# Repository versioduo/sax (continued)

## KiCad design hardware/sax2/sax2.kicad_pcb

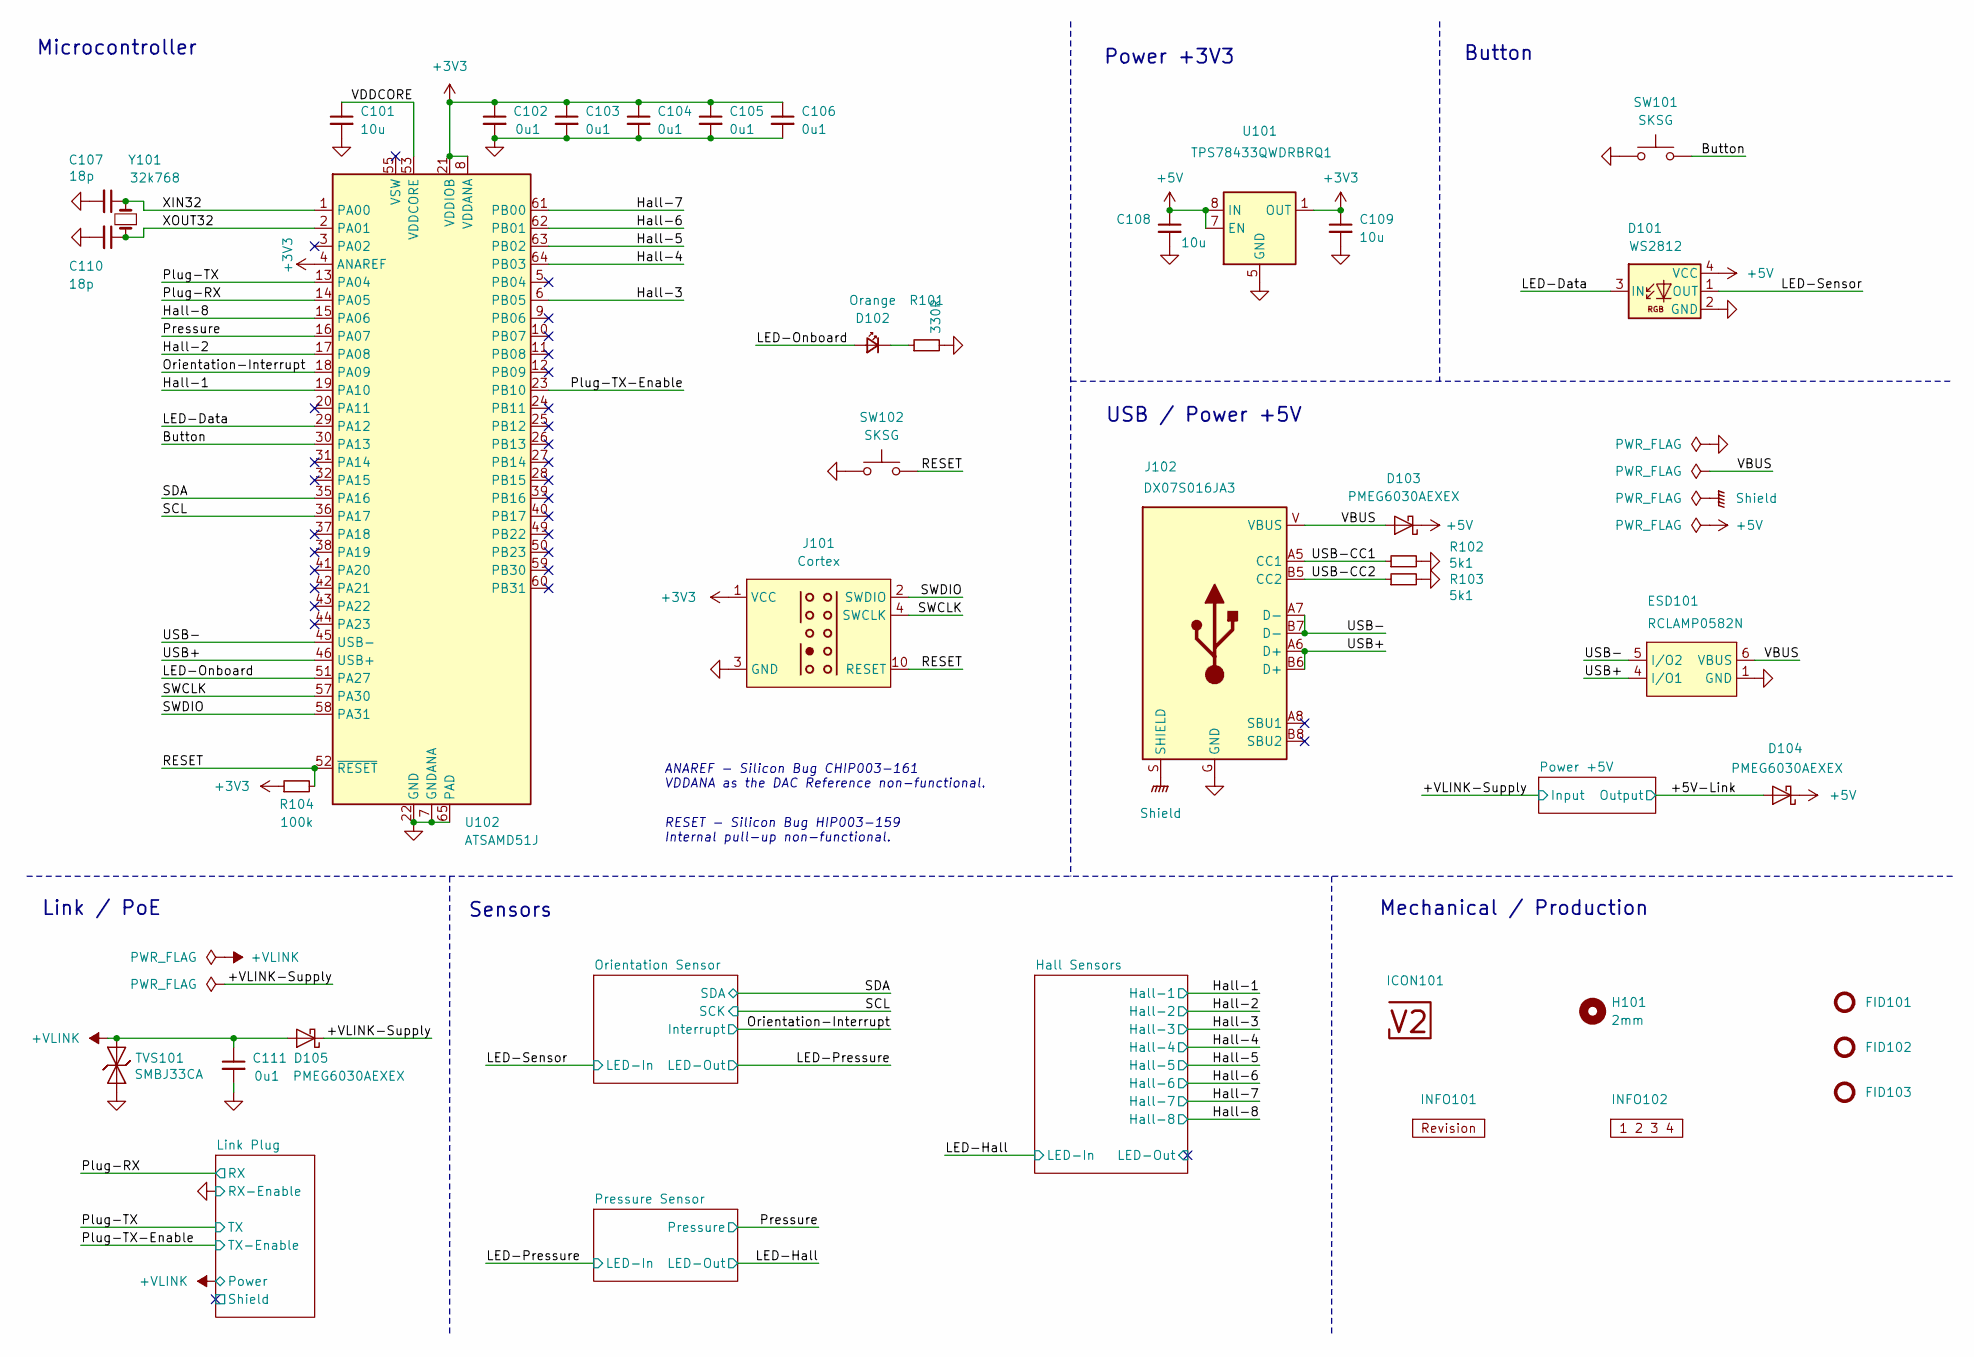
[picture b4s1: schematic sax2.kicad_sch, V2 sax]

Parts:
C101: 10u; C_0603; Rating 10V; Mouser 810-C1608X6S1A106M
C102, C103, C104, C105, C106, C111: 0u1; C_0603; Rating 50V; Mouser 810-CGA3E2X7R1H104MA
C107, C110: 18p; C_0603; Mouser 603-CC603JRNPO9BN180
C108, C109: 10u; C_0805; Rating 25V; Mouser 810-C2012X5R1E106K
D101: WS2812; WS2812-2020; LCSC C965555
D102: Orange; LED_0603; Mouser 755-SML-D12D1WT86
D103, D104, D105: PMEG6030AEXEX; D_SOD-123HP; Mouser 771-PMEG6030AEXEX
ESD101: RCLAMP0582N; SLP1210N6; Mouser 947-RCLAMP0582N.TCT
FID101, FID102, FID103: Fiducial_Paste; Fiducial_0.5mm_Mask1mm_Paste
H101: 2mm; MountingHole_2mm
ICON101: V2-logo; Logo_Small
INFO101: Revision
INFO102: Layer_Numbers
J101: Cortex
J102: DX07S016JA3; JAE_DX07S016JA3; Mouser 656-DX07S016JA3R1500
R101: 330R; R_0603; Rating 100mW; Mouser 71-CRCW0603330RFKEAC
R102, R103: 5k1; R_0603; Rating 100mW; Mouser 71-CRCW06035K10FKEAC
R104: 100k; R_0603; Rating 100mW; Mouser 71-CRCW0603100KFKEAC
SW101, SW102: SKSG; Mouser 688-SKSGACE010
TVS101: SMBJ33CA; D_SMB; Rating 33V; Mouser 652-SMBJ33CA-Q
U101: TPS78433QWDRBRQ1; VSON-8-1_3x3mm_P0.65_EP1.65x2.4mm; Mouser 595-TPS78433QWDRBRQ1
U102: ATSAMD51J; QFN-64-1EP_9x9mm_P0.5mm_EP4.8x4.8mm_ThermalVias; Mouser 556-ATSAMD51J19AMU
Y101: 32k768; Crystal_SMD_3215-2Pin_3.2x1.5mm; Mouser 815-ABS0716632.768KT

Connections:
+3V3: C102.1, C103.1, C104.1, C105.1, C106.1, C109.1, J101.1 (VCC), R104.1, U101.1 (OUT), U102.4 (ANAREF), U102.8 (VDDANA), U102.21 (VDDIOB), U102.34 (VDDIO), U102.48 (VDDIO), U102.56 (VDDIO); also elsewhere on the board
+5V: C108.1, D101.4 (VCC), D103.1 (K), D104.1 (K), U101.7 (EN), U101.8 (IN); also elsewhere on the board
+VLINK: C111.1, D105.2 (A), TVS101.2 (A); also elsewhere on the board
/+5V-Link: D104.2 (A); also elsewhere on the board
/+VLINK-Supply: D105.1 (K); also elsewhere on the board
/Button: SW101.2, U102.30 (PA13)
/Hall-1: U102.19 (PA10); also elsewhere on the board
/Hall-2: U102.17 (PA08); also elsewhere on the board
/Hall-3: U102.6 (PB05); also elsewhere on the board
/Hall-4: U102.64 (PB03); also elsewhere on the board
/Hall-5: U102.63 (PB02); also elsewhere on the board
/Hall-6: U102.62 (PB01); also elsewhere on the board
/Hall-7: U102.61 (PB00); also elsewhere on the board
/Hall-8: U102.15 (PA06); also elsewhere on the board
/LED-Data: D101.3 (IN), U102.29 (PA12)
/LED-Onboard: D102.2 (A), U102.51 (PA27)
/LED-Sensor: D101.1 (OUT); also elsewhere on the board
/Orientation-Interrupt: U102.18 (PA09); also elsewhere on the board
/Plug-RX: U102.14 (PA05); also elsewhere on the board
/Plug-TX: U102.13 (PA04); also elsewhere on the board
/Plug-TX-Enable: U102.23 (PB10); also elsewhere on the board
/Pressure: U102.16 (PA07); also elsewhere on the board
/RESET: J101.10 (RESET), R104.2, SW102.2, U102.52 (~RESET)
/SCL: U102.36 (PA17); also elsewhere on the board
/SDA: U102.35 (PA16); also elsewhere on the board
/SWCLK: J101.4 (SWCLK), U102.57 (PA30)
/SWDIO: J101.2 (SWDIO), U102.58 (PA31)
/USB+: ESD101.4 (I/O1), J102.A6 (D+), J102.B6 (D+), U102.46 (USB+)
/USB-: ESD101.5 (I/O2), J102.A7 (D-), J102.B7 (D-), U102.45 (USB-)
/USB-CC1: J102.A5 (CC1), R102.1
/USB-CC2: J102.B5 (CC2), R103.1
/VBUS: D103.2 (A), ESD101.6 (VBUS), J102.V (VBUS)
/VDDCORE: C101.1, U102.53 (VDDCORE)
/XIN32: C107.1, U102.1 (PA00), Y101.2
/XOUT32: C110.1, U102.2 (PA01), Y101.1
GND: C101.2, C102.2, C103.2, C104.2, C105.2, C106.2, C107.2, C108.2, C109.2, C110.2, C111.2, D101.2 (GND), ESD101.1 (GND), J101.3 (GND), J101.5 (GND), J102.G (GND), R101.2, R102.2, R103.2, SW101.1, SW102.1, TVS101.1 (K), U101.5 (GND), U101.9 (GND), U102.7 (GNDANA), U102.22 (GND), U102.33 (GND), U102.47 (GND), U102.54 (GND), U102.65 (PAD); also elsewhere on the board
unnamed: D102.1 (K), R101.1
Shield: J102.S (SHIELD)

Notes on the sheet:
ANAREF - Silicon Bug CHIP003-161 VDDANA as the DAC Reference non-functional.
Sensors
Link / PoE
RESET - Silicon Bug HIP003-159 Internal pull-up non-functional.
Button
Power +3V3
Mechanical / Production
Microcontroller
USB / Power +5V

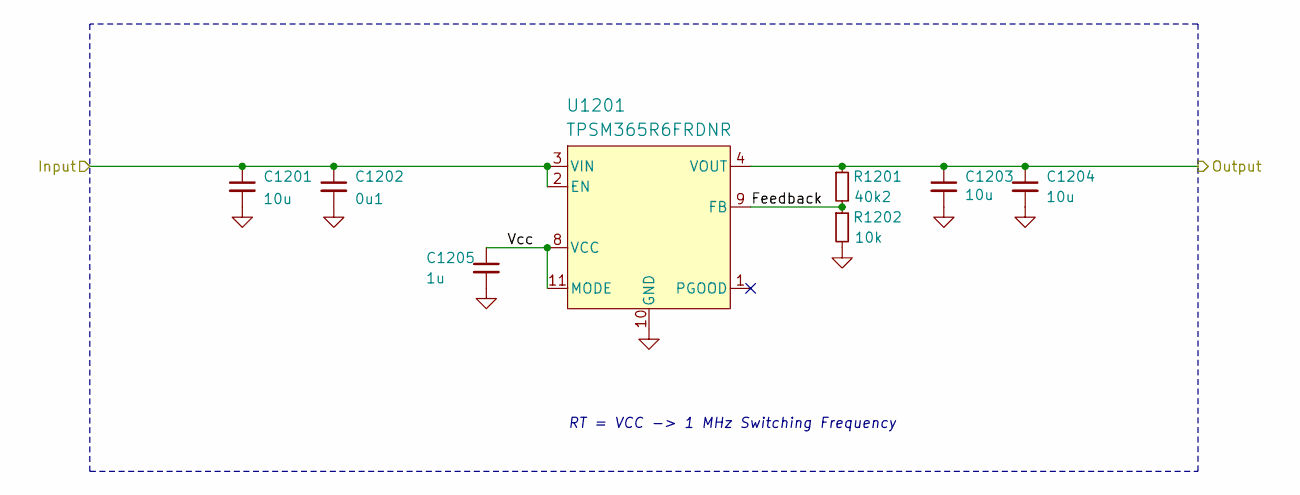
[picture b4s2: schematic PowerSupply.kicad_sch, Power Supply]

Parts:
C1201: 10u; C_1210; Rating 50V; Mouser 810-CNA6P1X7R1H106K2
C1202: 0u1; C_0603; Rating 50V; Mouser 810-CGA3E2X7R1H104MA
C1203, C1204: 10u; C_1210; Rating 25V; Mouser 810-CGA6P3X7R1E226M5
C1205: 1u; C_0603; Rating 50V; Mouser 810-CGA3E3X7R1H105K0
R1201: 40k2; R_0603; Rating 500mW; Mouser 71-RCS060340K2FKEA
R1202: 10k; R_0603; Rating 100mW; Mouser 71-CRCW060310K0FKEAC
U1201: TPSM365R6FRDNR; QFN-11; Rating 600mA; Mouser 595-TPSM365R6FRDNR

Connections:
/+5V-Link: C1203.1, C1204.1, R1201.1, U1201.4 (VOUT); also elsewhere on the board
/+VLINK-Supply: C1201.1, C1202.1, U1201.2 (EN), U1201.3 (VIN); also elsewhere on the board
/Power +5V/Feedback: R1201.2, R1202.1, U1201.9 (FB)
/Power +5V/Vcc: C1205.1, U1201.8 (VCC), U1201.11 (MODE)
GND: C1201.2, C1202.2, C1203.2, C1204.2, C1205.2, R1202.2, U1201.10 (GND); also elsewhere on the board

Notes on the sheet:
RT = VCC -> 1 MHz Switching Frequency

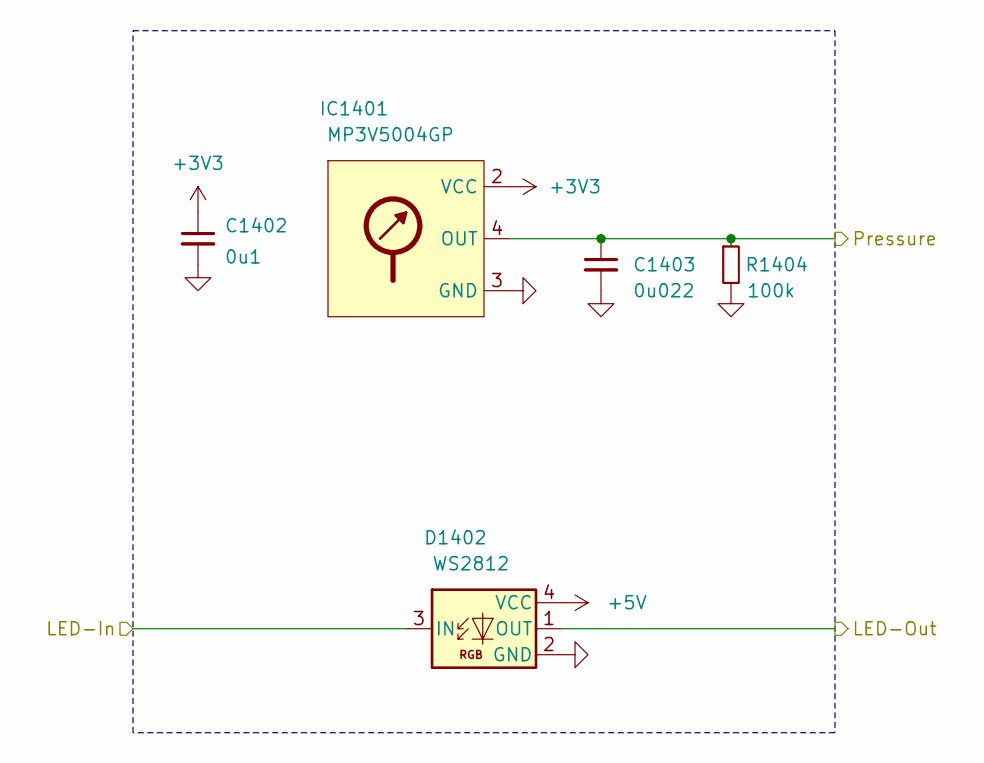
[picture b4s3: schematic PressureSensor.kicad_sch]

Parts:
C1402: 0u1; C_0603; Rating 50V; Mouser 810-CGA3E2X7R1H104MA
C1403: 0u022; C_0603; Mouser 603-CC603KPX7R9BB223
D1402: WS2812; WS2812-2020; LCSC C965555
IC1401: MP3V5004GP; Mouser 841-MP3V5004GP
R1404: 100k; R_0603; Rating 100mW; Mouser 71-CRCW0603100KFKEAC

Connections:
+3V3: C1402.1, IC1401.2 (VCC); also elsewhere on the board
+5V: D1402.4 (VCC); also elsewhere on the board
/LED-Hall: D1402.1 (OUT); also elsewhere on the board
/LED-Pressure: D1402.3 (IN); also elsewhere on the board
/Pressure: C1403.1, IC1401.4 (OUT), R1404.1; also elsewhere on the board
GND: C1402.2, C1403.2, D1402.2 (GND), IC1401.3 (GND), R1404.2; also elsewhere on the board

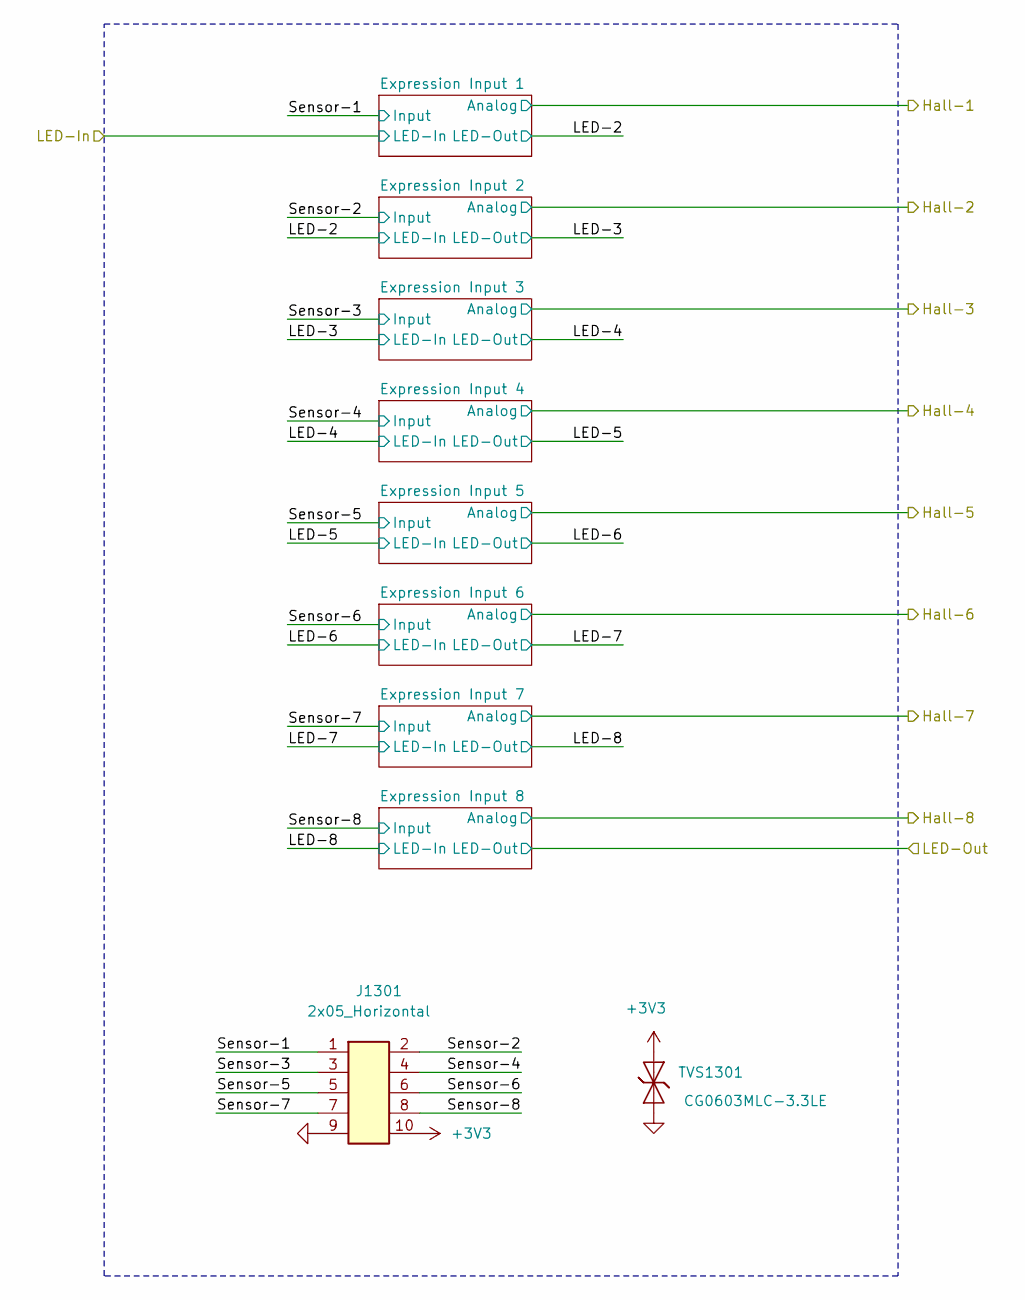
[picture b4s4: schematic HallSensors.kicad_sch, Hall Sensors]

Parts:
J1301: 2x05_Horizontal; PinHeader_2x05_P1.27mm_Horizontal; Mouser 649-200211120001T4LF
TVS1301: CG0603MLC-3.3LE; D_0603; Rating 3V3; Mouser 652-CG0603MLC-3.3LE

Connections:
+3V3: J1301.10, TVS1301.1 (K); also elsewhere on the board
/Hall Sensors/Sensor-1: J1301.1; also elsewhere on the board
/Hall Sensors/Sensor-2: J1301.2; also elsewhere on the board
/Hall Sensors/Sensor-3: J1301.3; also elsewhere on the board
/Hall Sensors/Sensor-4: J1301.4; also elsewhere on the board
/Hall Sensors/Sensor-5: J1301.5; also elsewhere on the board
/Hall Sensors/Sensor-6: J1301.6; also elsewhere on the board
/Hall Sensors/Sensor-7: J1301.7; also elsewhere on the board
/Hall Sensors/Sensor-8: J1301.8; also elsewhere on the board
GND: J1301.9, TVS1301.2 (A); also elsewhere on the board

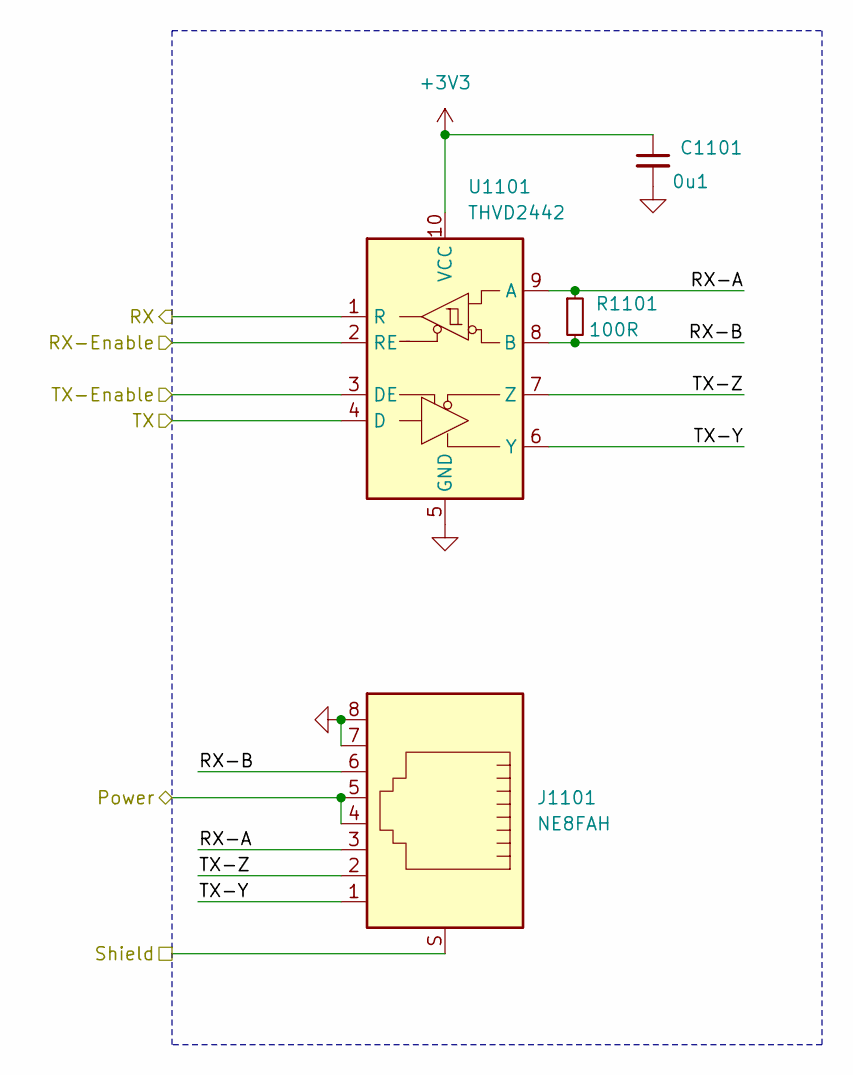
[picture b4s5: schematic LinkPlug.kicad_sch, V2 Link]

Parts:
C1101: 0u1; C_0603; Rating 50V; Mouser 810-CGA3E2X7R1H104MA
J1101: NE8FAH; Mouser 568-NE8FAH
R1101: 100R; R_0603; Rating 330mW; Mouser 71-CRCW0603100RFKEAH
U1101: THVD2442; VSON-10-4-1EP_3x3mm_P0.5mm_EP1.65x2.4mm_ThermalVias; Mouser 595-THVD2442DRCR

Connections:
+3V3: C1101.1, U1101.10 (VCC); also elsewhere on the board
+VLINK: J1101.4, J1101.5; also elsewhere on the board
/Link Plug/RX-A: J1101.3, R1101.1, U1101.9 (A)
/Link Plug/RX-B: J1101.6, R1101.2, U1101.8 (B)
/Link Plug/Shield: J1101.S
/Link Plug/TX-Y: J1101.1, U1101.6 (Y)
/Link Plug/TX-Z: J1101.2, U1101.7 (Z)
/Plug-RX: U1101.1 (R); also elsewhere on the board
/Plug-TX: U1101.4 (D); also elsewhere on the board
/Plug-TX-Enable: U1101.3 (DE); also elsewhere on the board
GND: C1101.2, J1101.7, J1101.8, U1101.2 (RE), U1101.5 (GND), U1101.11 (GND); also elsewhere on the board

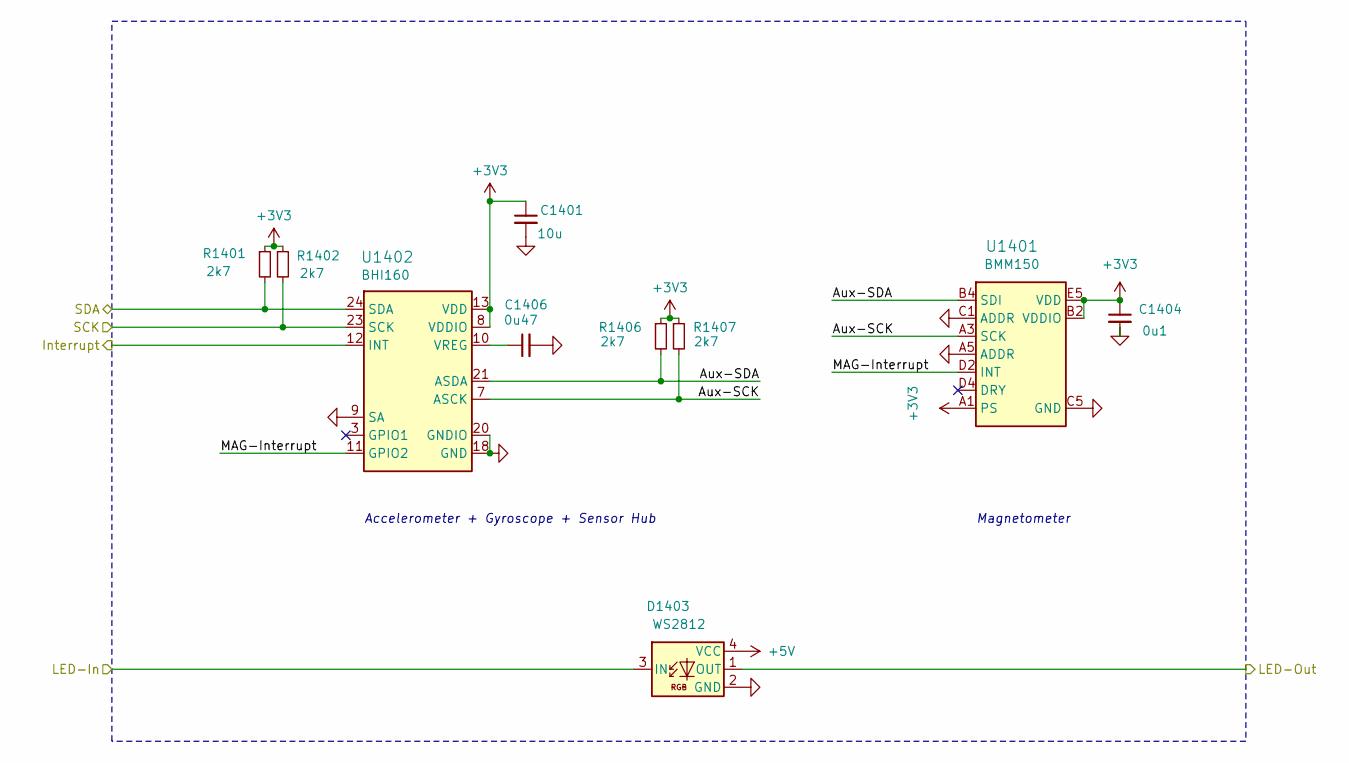
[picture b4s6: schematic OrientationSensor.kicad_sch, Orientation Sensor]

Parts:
C1401: 10u; C_0603; Rating 10V; Mouser 810-C1608X6S1A106M
C1404: 0u1; C_0603; Rating 50V; Mouser 810-CGA3E2X7R1H104MA
C1406: 0u47; C_0603; Mouser 603-CC0603JR6BB474
D1403: WS2812; WS2812-2020; LCSC C965555
R1401, R1402, R1406, R1407: 2k7; R_0603; Rating 100mW; Mouser 71-CRCW06032K70FKEAC
U1401: BMM150; WLCSP-1.56x1.56; LCSC C171681
U1402: BHI160; LGA24-3x3; LCSC C464452

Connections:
+3V3: C1401.1, C1404.1, R1401.1, R1402.1, R1406.1, R1407.1, U1401.A1 (PS), U1401.B2 (VDDIO), U1401.E5 (VDD), U1402.8 (VDDIO), U1402.13 (VDD); also elsewhere on the board
+5V: D1403.4 (VCC); also elsewhere on the board
/LED-Pressure: D1403.1 (OUT); also elsewhere on the board
/LED-Sensor: D1403.3 (IN); also elsewhere on the board
/Orientation Sensor/Aux-SCK: R1407.2, U1401.A3 (SCK), U1402.7 (ASCK)
/Orientation Sensor/Aux-SDA: R1406.2, U1401.B4 (SDI), U1402.21 (ASDA)
/Orientation Sensor/MAG-Interrupt: U1401.D2 (INT), U1402.11 (GPIO2)
/Orientation-Interrupt: U1402.12 (INT); also elsewhere on the board
/SCL: R1402.2, U1402.23 (SCK); also elsewhere on the board
/SDA: R1401.2, U1402.24 (SDA); also elsewhere on the board
GND: C1401.2, C1404.2, C1406.2, D1403.2 (GND), U1401.A5 (ADDR), U1401.C1 (ADDR), U1401.C5 (GND), U1401.E1 (GND), U1401.E3 (GND), U1402.9 (SA), U1402.18 (GND), U1402.20 (GNDIO); also elsewhere on the board
unnamed: C1406.1, U1402.10 (VREG)

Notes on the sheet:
Accelerometer + Gyroscope + Sensor Hub
Magnetometer

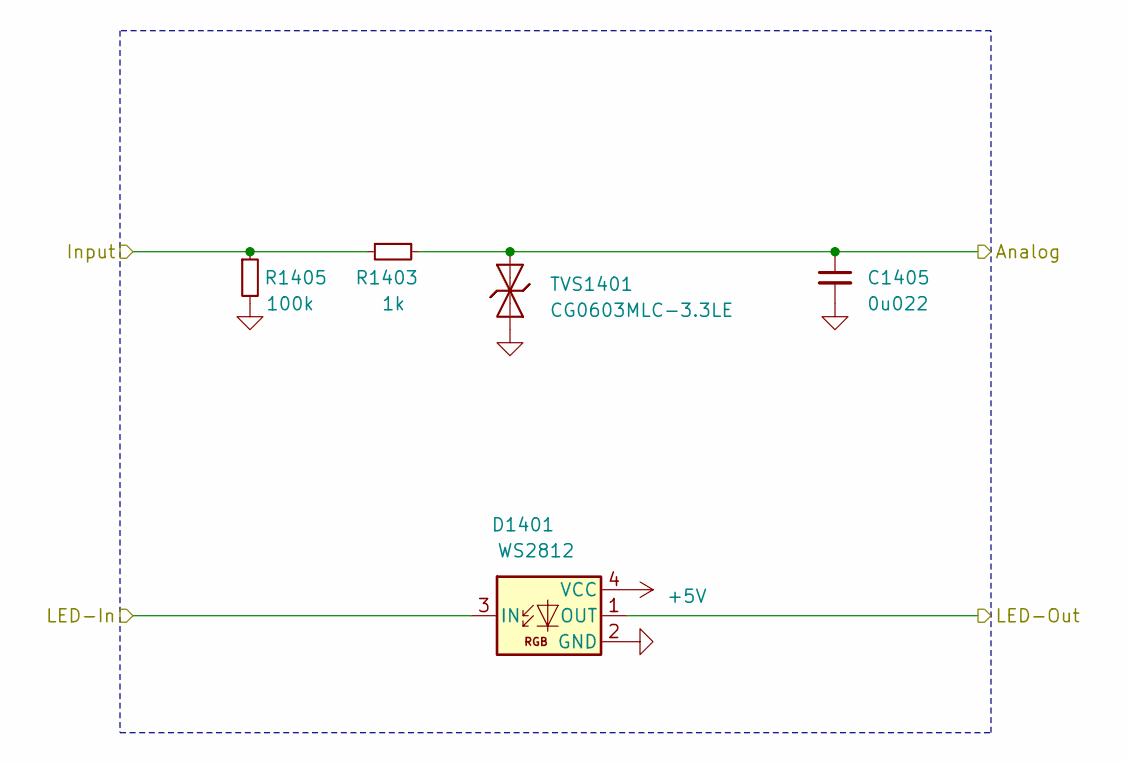
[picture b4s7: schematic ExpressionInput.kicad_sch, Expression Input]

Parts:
C1405: 0u022; C_0603; Mouser 603-CC603KPX7R9BB223
D1401: WS2812; WS2812-2020; LCSC C965555
R1403: 1k; R_0603; Rating 330mW; Mouser 71-CRCW06031K00FKEAH
R1405: 100k; R_0603; Rating 100mW; Mouser 71-CRCW0603100KFKEAC
TVS1401: CG0603MLC-3.3LE; D_0603; Rating 3V3; Mouser 652-CG0603MLC-3.3LE

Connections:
+5V: D1401.4 (VCC); also elsewhere on the board
/Hall Sensors/LED-2: D1401.1 (OUT); also elsewhere on the board
/Hall Sensors/Sensor-1: R1403.2, R1405.1; also elsewhere on the board
/Hall-1: C1405.1, R1403.1, TVS1401.2 (A); also elsewhere on the board
/LED-Hall: D1401.3 (IN); also elsewhere on the board
GND: C1405.2, D1401.2 (GND), R1405.2, TVS1401.1 (K); also elsewhere on the board

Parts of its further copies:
C1501, C1601, C1701, C1801, C1901, C2001, C2101: 0u022; C_0603; Mouser 603-CC603KPX7R9BB223
D1501, D1601, D1701, D1801, D1901, D2001, D2101: WS2812; WS2812-2020; LCSC C965555
R1501, R1601, R1701, R1801, R1901, R2001, R2101: 1k; R_0603; Rating 330mW; Mouser 71-CRCW06031K00FKEAH
R1502, R1602, R1702, R1802, R1902, R2002, R2102: 100k; R_0603; Rating 100mW; Mouser 71-CRCW0603100KFKEAC
TVS1501, TVS1601, TVS1701, TVS1801, TVS1901, TVS2001, TVS2101: CG0603MLC-3.3LE; D_0603; Rating 3V3; Mouser 652-CG0603MLC-3.3LE

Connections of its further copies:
+5V: D1501.4 (VCC), D1601.4 (VCC), D1701.4 (VCC), D1801.4 (VCC), D1901.4 (VCC), D2001.4 (VCC), D2101.4 (VCC); also elsewhere on the board
/Hall Sensors/LED-2: D1501.3 (IN); also elsewhere on the board
/Hall Sensors/LED-3: D1501.1 (OUT), D1601.3 (IN)
/Hall Sensors/LED-4: D1601.1 (OUT), D1701.3 (IN)
/Hall Sensors/LED-5: D1701.1 (OUT), D1801.3 (IN)
/Hall Sensors/LED-6: D1801.1 (OUT), D1901.3 (IN)
/Hall Sensors/LED-7: D1901.1 (OUT), D2001.3 (IN)
/Hall Sensors/LED-8: D2001.1 (OUT), D2101.3 (IN)
/Hall Sensors/LED-Out: D2101.1 (OUT)
/Hall Sensors/Sensor-2: R1501.2, R1502.1; also elsewhere on the board
/Hall Sensors/Sensor-3: R1601.2, R1602.1; also elsewhere on the board
/Hall Sensors/Sensor-4: R1701.2, R1702.1; also elsewhere on the board
/Hall Sensors/Sensor-5: R1801.2, R1802.1; also elsewhere on the board
/Hall Sensors/Sensor-6: R1901.2, R1902.1; also elsewhere on the board
/Hall Sensors/Sensor-7: R2001.2, R2002.1; also elsewhere on the board
/Hall Sensors/Sensor-8: R2101.2, R2102.1; also elsewhere on the board
/Hall-2: C1501.1, R1501.1, TVS1501.2 (A); also elsewhere on the board
/Hall-3: C1601.1, R1601.1, TVS1601.2 (A); also elsewhere on the board
/Hall-4: C1701.1, R1701.1, TVS1701.2 (A); also elsewhere on the board
/Hall-5: C1801.1, R1801.1, TVS1801.2 (A); also elsewhere on the board
/Hall-6: C1901.1, R1901.1, TVS1901.2 (A); also elsewhere on the board
/Hall-7: C2001.1, R2001.1, TVS2001.2 (A); also elsewhere on the board
/Hall-8: C2101.1, R2101.1, TVS2101.2 (A); also elsewhere on the board
GND: C1501.2, C1601.2, C1701.2, C1801.2, C1901.2, C2001.2, C2101.2, D1501.2 (GND), D1601.2 (GND), D1701.2 (GND), D1801.2 (GND), D1901.2 (GND), D2001.2 (GND), D2101.2 (GND), R1502.2, R1602.2, R1702.2, R1802.2, R1902.2, R2002.2, R2102.2, TVS1501.1 (K), TVS1601.1 (K), TVS1701.1 (K), TVS1801.1 (K), TVS1901.1 (K), TVS2001.1 (K), TVS2101.1 (K); also elsewhere on the board

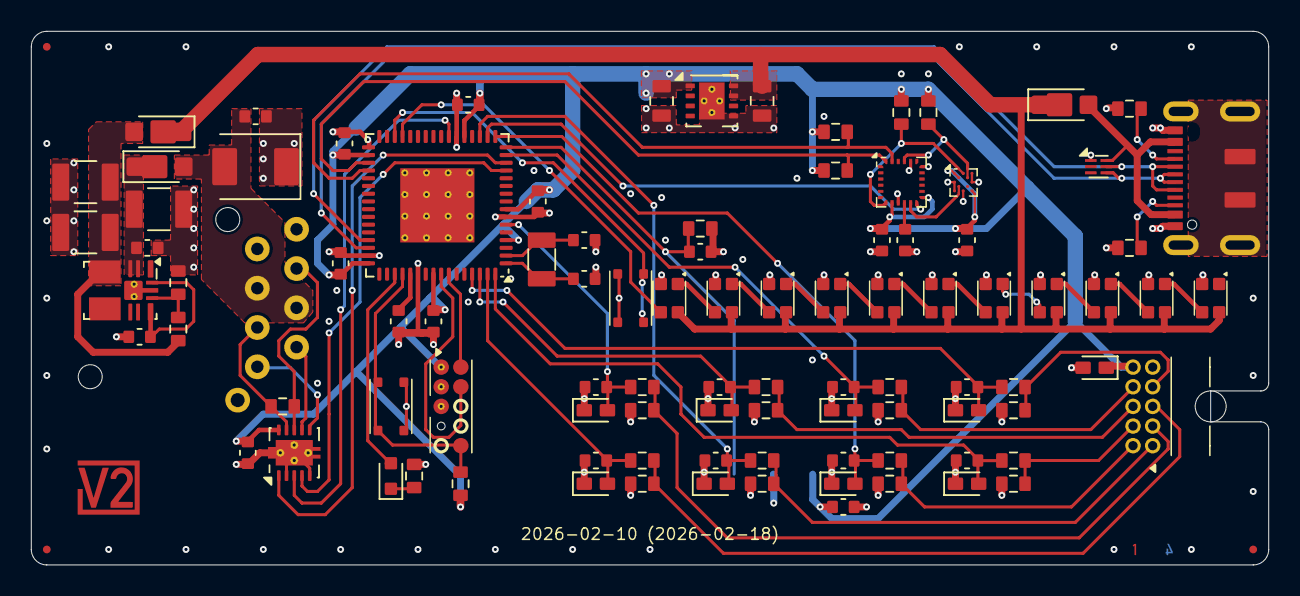
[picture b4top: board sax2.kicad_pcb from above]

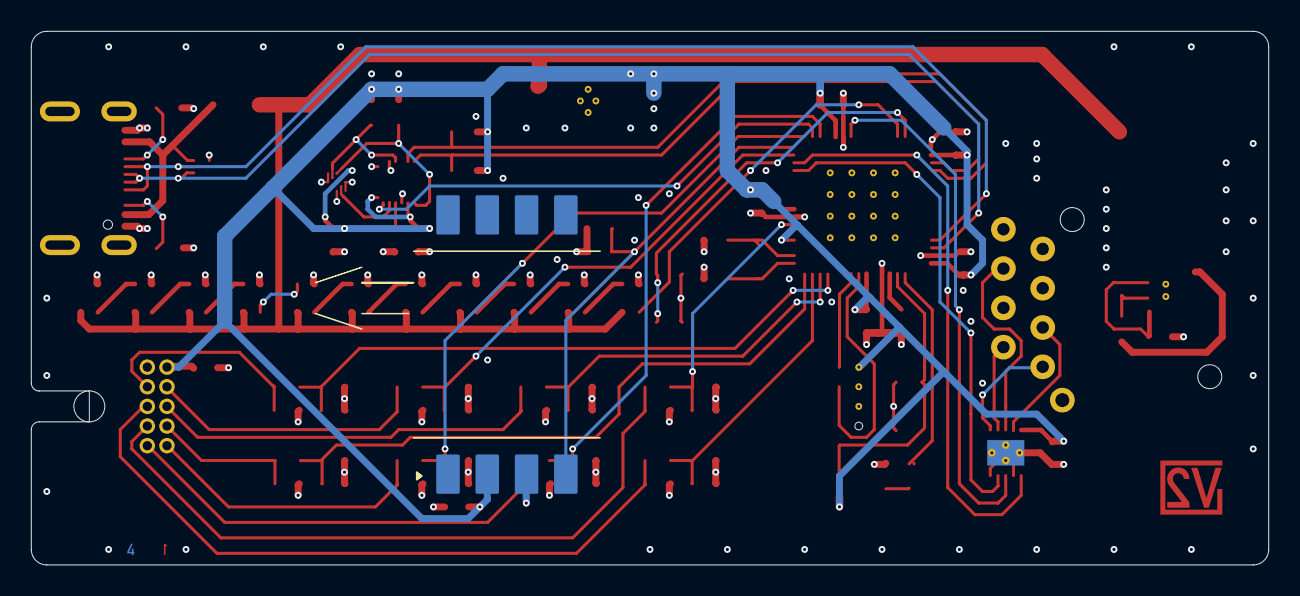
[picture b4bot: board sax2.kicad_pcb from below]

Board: 4 copper layers, 80.0 x 34.5 mm, 105 parts (2 on the bottom side), 64 nets.

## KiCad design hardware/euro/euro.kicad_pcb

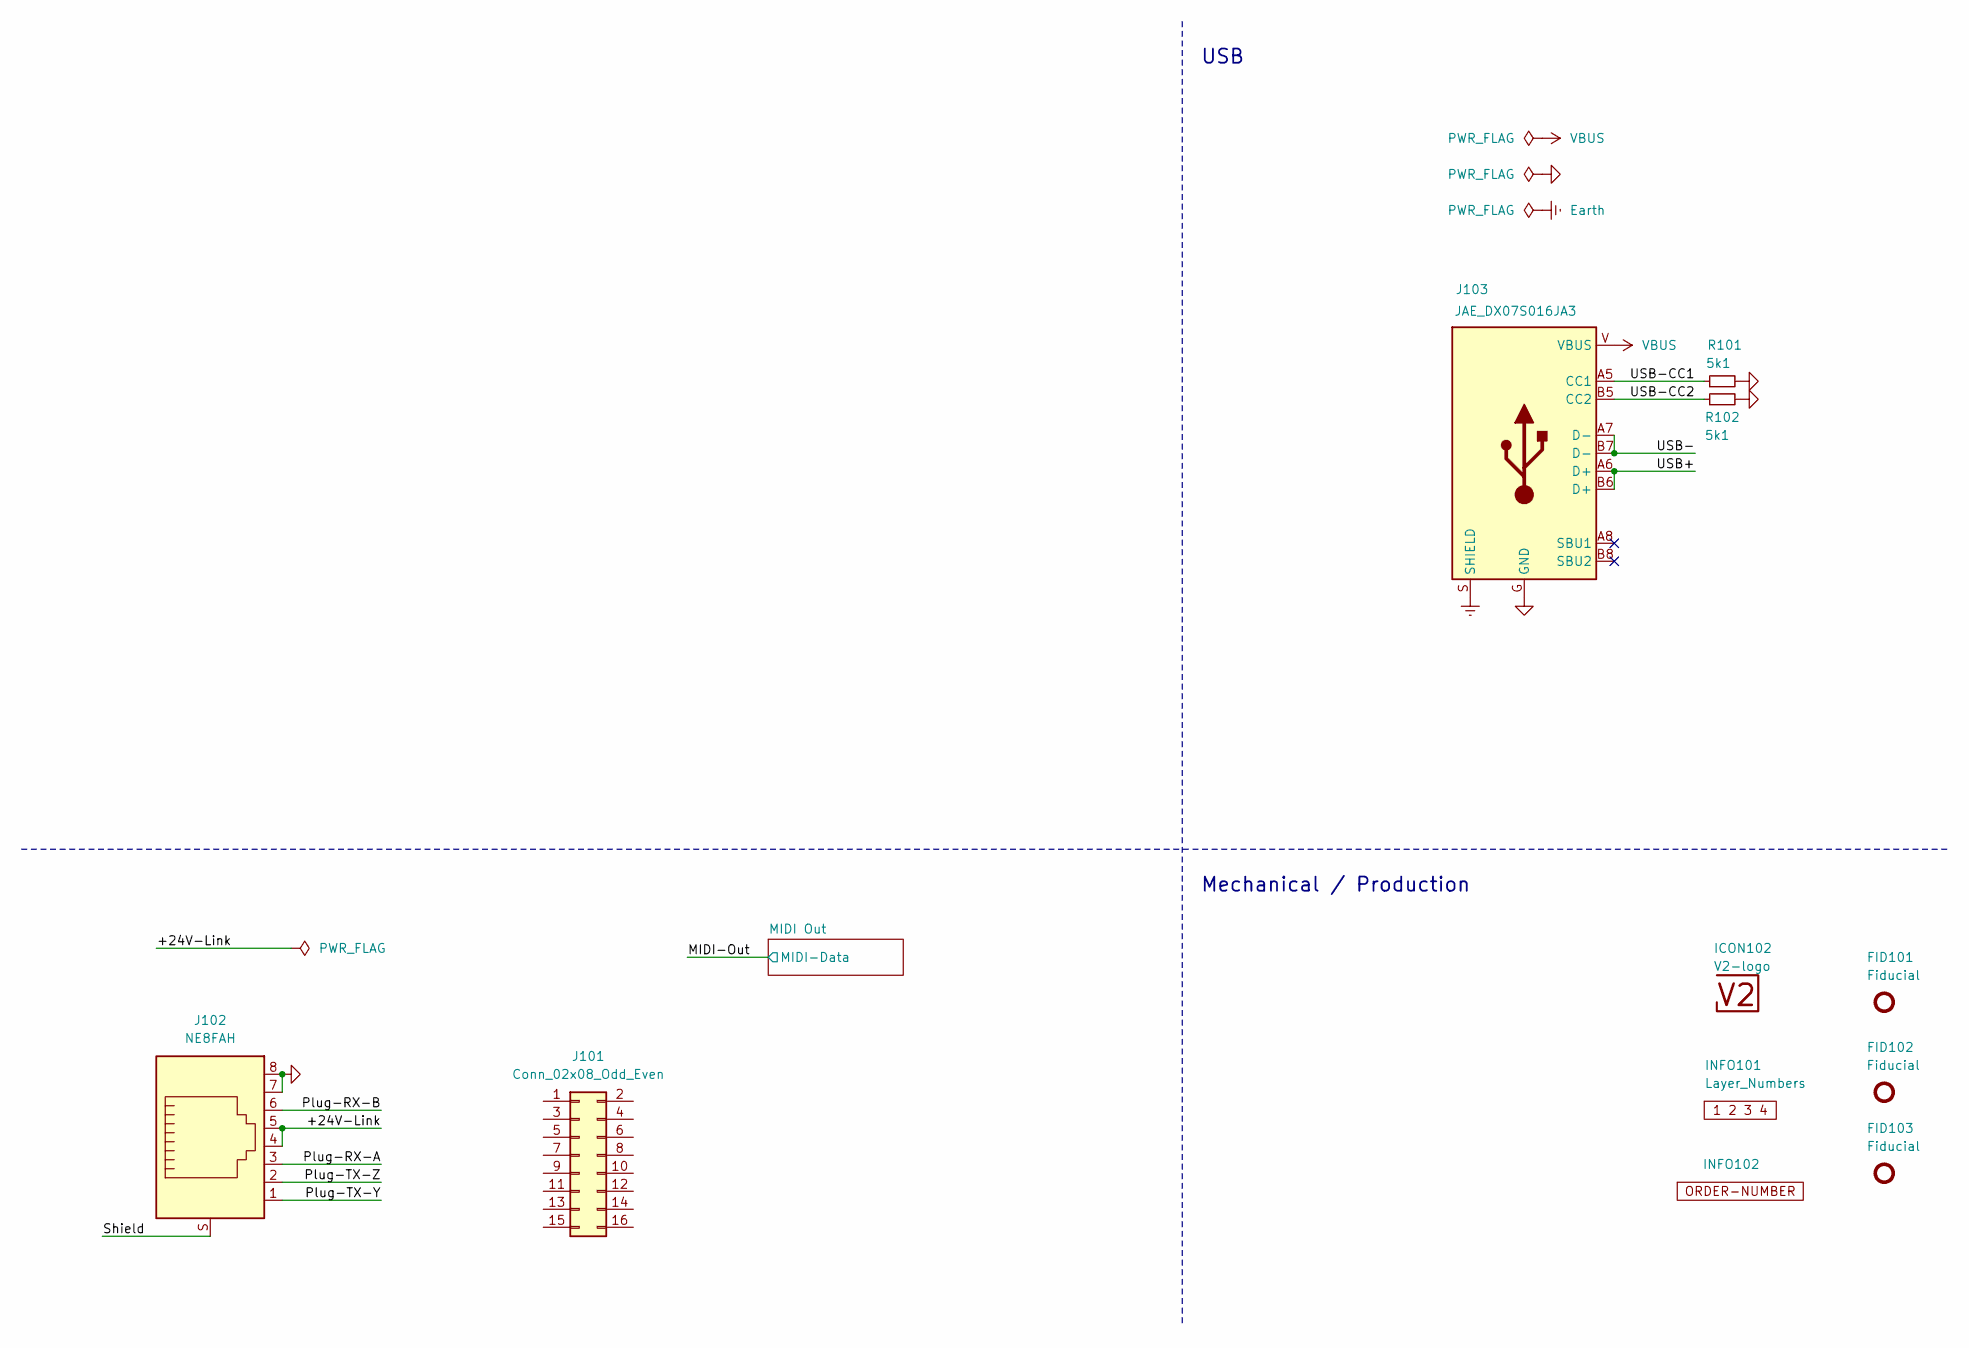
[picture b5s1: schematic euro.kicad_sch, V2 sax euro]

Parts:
FID101, FID102, FID103: Fiducial; Fiducial_0.5mm_Mask1mm_Paste
ICON102: V2-logo; Logo_Tiny
INFO101: Layer_Numbers
INFO102: ORDER-NUMBER; Order_Number
J101: Conn_02x08_Odd_Even; IDC-Header_2x08_P2.54mm_Horizontal
J102: NE8FAH
J103: JAE_DX07S016JA3
R101, R102: 5k1; R_0603_1608Metric

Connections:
/+24V-Link: J102.4, J102.5
/Plug-RX-A: J102.3
/Plug-RX-B: J102.6
/Plug-TX-Y: J102.1
/Plug-TX-Z: J102.2
/Shield: J102.S
/USB+: J103.A6 (D+), J103.B6 (D+)
/USB-: J103.A7 (D-), J103.B7 (D-)
/USB-CC1: J103.A5 (CC1), R101.1
/USB-CC2: J103.B5 (CC2), R102.1
Earth: J103.S (SHIELD)
GND: J102.7, J102.8, J103.G (GND), R101.2, R102.2; also elsewhere on the board
VBUS: J103.V (VBUS)

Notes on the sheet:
Mechanical / Production
USB

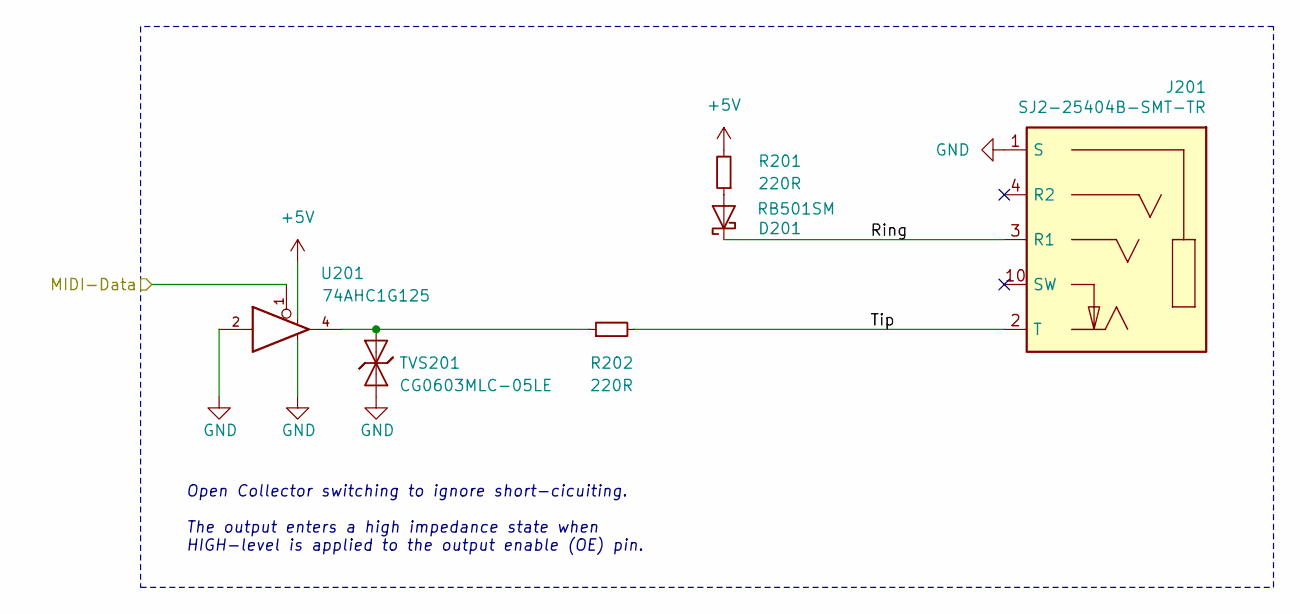
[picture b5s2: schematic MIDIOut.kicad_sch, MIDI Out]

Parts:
D201: RB501SM; D_SOD-523
J201: SJ2-25404B-SMT-TR; CUI_SJ2-25404B-SMT-TR
R201, R202: 220R; R_0603_1608Metric
TVS201: CG0603MLC-05LE; D_0603_1608Metric
U201: 74AHC1G125; SOT-23-5

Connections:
+5V: R201.2, U201.5
/MIDI Out/Ring: D201.1 (K), J201.3 (R1)
/MIDI Out/Tip: J201.2 (T), R202.2
/MIDI-Out: U201.1
GND: J201.1 (S), TVS201.1 (K), U201.2, U201.3; also elsewhere on the board
unnamed: D201.2 (A), R201.1
unnamed: R202.1, TVS201.2 (A), U201.4

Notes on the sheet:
﻿Open Collector switching to ignore short-cicuiting. The output enters a high impedance state when HIGH-level is applied to the output enable (OE) pin.

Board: 4 copper layers, 17 parts (0 on the bottom side), 11 nets, no tracks yet.

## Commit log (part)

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2025-12-29 Import
2025-12-31 Add sax euro
2026-01-04 Refresh
2026-01-15 Add V2 Link support
2026-01-15 Update library
2026-01-15 Add accelerometer
2026-01-19 Add sax2
2026-01-22 Refreseh
2026-01-22 Refresh footprints
2026-01-29 Update sensors
2026-02-05 Udpate I2C
2026-02-13 Replace Order_Number
2026-02-15 Add sax-connect
2026-02-17 Update firmware
2026-02-17 Add serial MIDI
2026-02-19 New surface
2026-02-20 Update note timing
2026-02-21 Update calibration
2026-02-22 Add pressure
2026-02-22 sax2 -> sax
2026-02-25 Export stencil
2026-03-14 Update ESD suppressor
2026-03-16 Remap pressure
2026-03-22 KiCad 10
2026-03-23 Update calibration logic
2026-03-24 Add Link ping
2026-03-26 Ping
2026-03-26 Update connect
2026-03-29 Update Revision footprint
2026-03-31 Replace step-down
2026-03-31 Fix inverting logic
2026-04-04 Limit up note length to 3 seconds
2026-04-09 Disable orientation and pressure
2026-04-12 Swap connect colors
2026-04-12 Add AllNotesOff
2026-04-24 Update DRC
2026-05-11 Good Bye Imperial
2026-06-21 Update MIDI API
2026-06-23 Update V2MIDI API
